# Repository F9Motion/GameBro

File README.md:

# GameBro
Custom portotive gaming console with Android OS, 5 buttons, joystick and display. I did this for playing minecraft Pocket edition and other games.

# Why I did this
I like minecraft and at school teachers before lesson take form students phones. This console is good for spent boring time (I don't play in lesson time don't worry)
# Features
1. This is full station for Android.
2. You can just install all games which you want and download to this!
3. Very cool :D.
4. With joystick you can control the mouse like in windows.
5. Compack: Easy to take outside
# How it works
The **Rodxa CM5** is full android station so almost all works do this Rodxa. And this 5 buttons and joystick connected to **Raspberry pi pico** and pico controls only this. **I don't place Wifi and Bluetooth module** because I don't think it's very important and you can just econome in this.
# How to assemble
1. Order PCB form JLCPCB
2. Order all parts for this GameBro (You can find parts in BOM)
3. Solder parts to PCB
4. Print CAD
5. And just assemble all of this
# Bill of Materials (BOM)
|Name                          |Cost   |Link                     |
|------------------------------|-------|-------------------------|
|Radxa cm5                     |$182.16|https://ali.click/m5rxp1e|
|Raspberry pi pico             |$3.47  |https://ali.click/i4rxp1a|
|Joystick                      |$0.92  |https://ali.click/q3rxp14|
|Buttons                       |$0.5   |https://ali.click/q2rxp1s|
|HDMI socket                   |$0.71  |https://ali.click/bdrxp15|
|Type-C socket                 |$1.02  |https://ali.click/cfrxp1w|
|Printing PCB                  |$4.20  |order from JLCPCB        |
|Felament price for 3D printing|       |                         |
|buttons.step                  |$0.01  |Printing legion          |
|bottom.step                   |$0.97  |Printing legion          |
|top.step                      |$0.21  |Printing legion          |
|TOTAL                         |$194.17|                         |
# Credits
All of work done by Rasul
# Sponsors
Hack club forge (https://forge.hackclub.com/)

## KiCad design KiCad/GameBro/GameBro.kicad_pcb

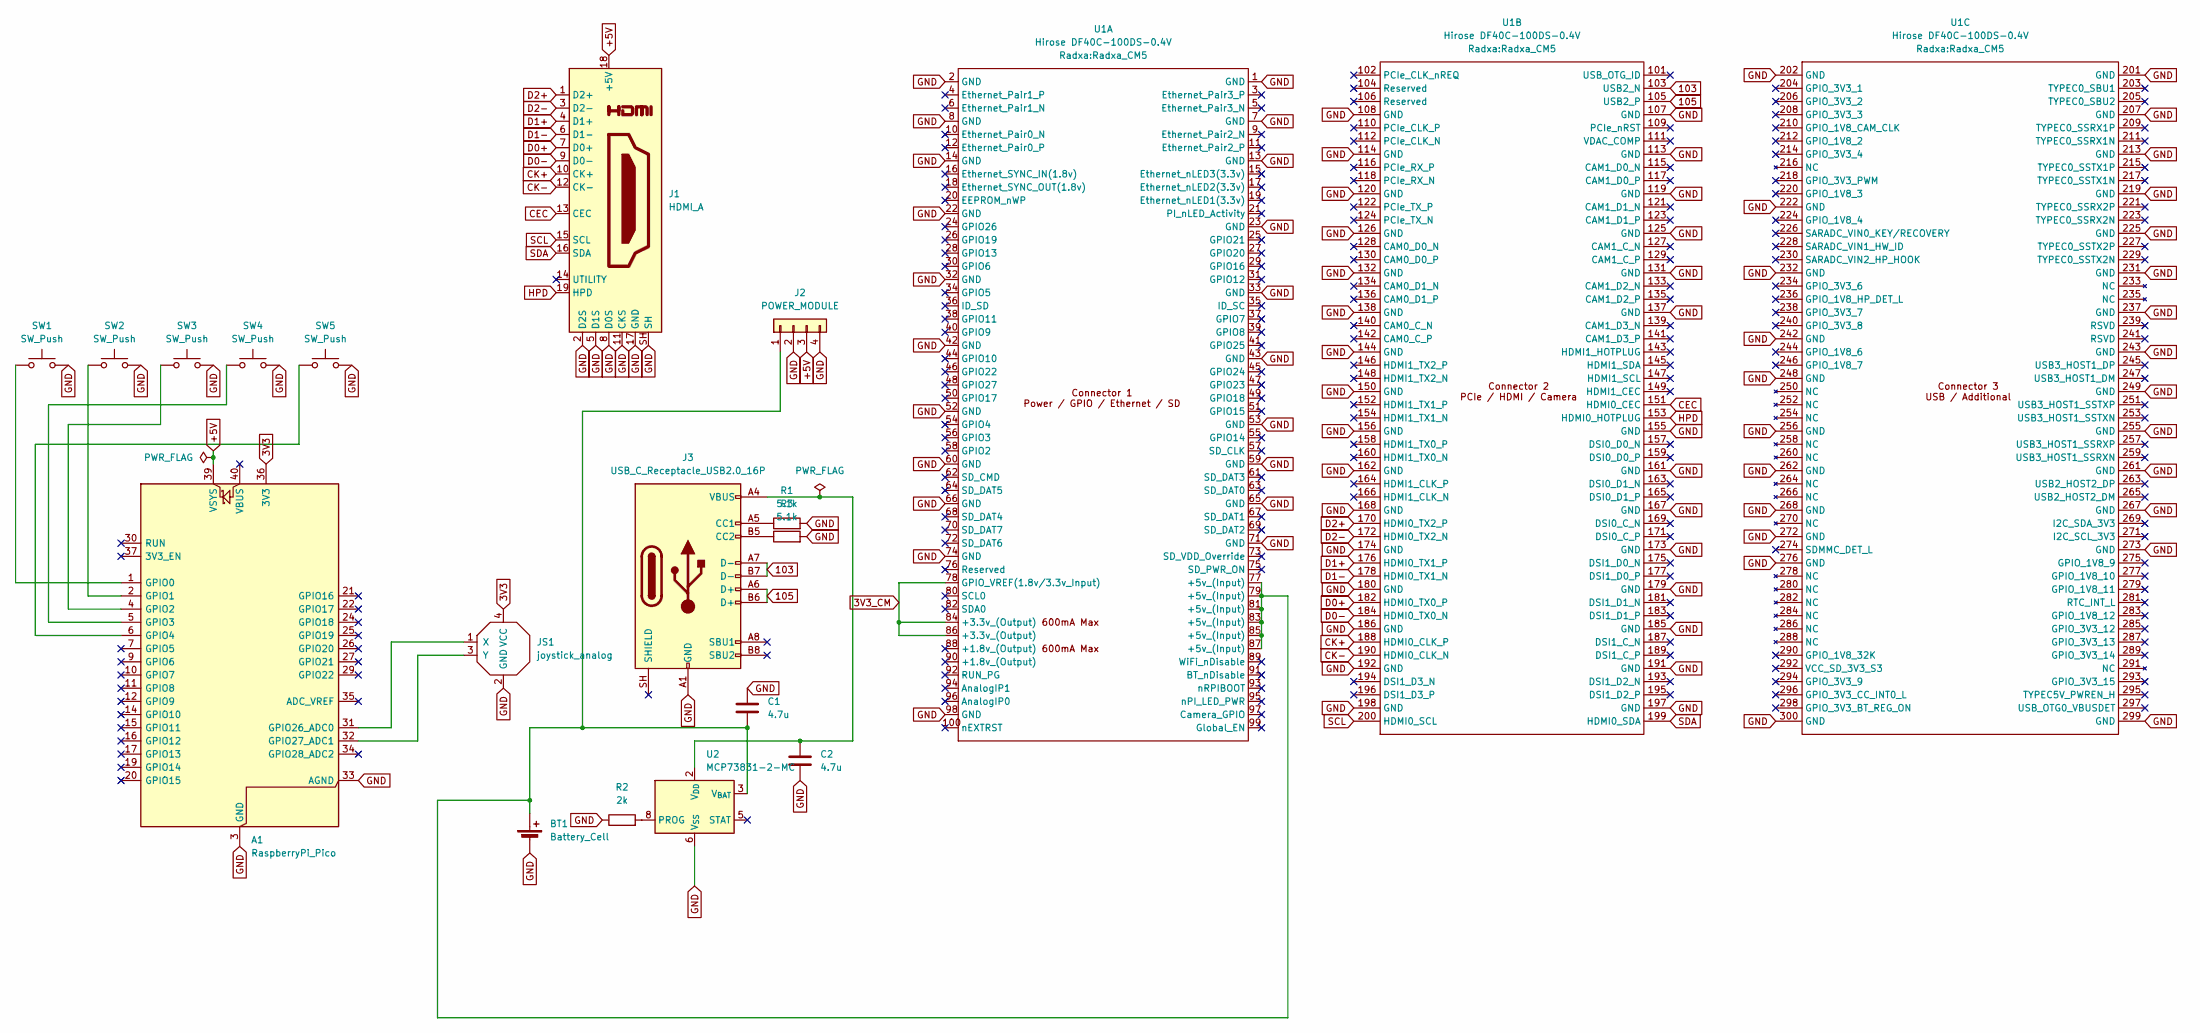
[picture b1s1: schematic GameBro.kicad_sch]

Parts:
A1: RaspberryPi_Pico; RaspberryPi_Pico_Common_Unspecified
BT1: Battery_Cell; JST_PH_B2B-PH-K_1x02_P2.00mm_Vertical
C1, C2: 4.7u; C_0805_2012Metric
J1: HDMI_A; HDMI_A_Molex_208658-1001_Horizontal
J2: POWER_MODULE; PinHeader_1x04_P2.54mm_Vertical
J3: USB_C_Receptacle_USB2.0_16P; USB_C_Receptacle_HRO_TYPE-C-31-M-12
JS1: joystick_analog; JOYSTICK-PSP1000
R1, R3: 5.1k; R_0603_1608Metric
R2: 2k; R_0603_1608Metric
SW1, SW2, SW3, SW4, SW5: SW_Push; SW_SPST_PTS810
U1: Hirose DF40C-100DS-0.4V; Radxa_CM5
U2: MCP73831-2-MC; Radxa_CM5

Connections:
3V3: A1.36 (3V3), JS1.4 (VCC)
3V3_CM: U1.78 (GPIO_VREF(1.8v/3.3v_Input)), U1.84 (+3.3v_(Output)), U1.86 (+3.3v_(Output))
103: J3.A7 (D-), J3.B7 (D-), U1.103 (USB2_N)
105: J3.A6 (D+), J3.B6 (D+), U1.105 (USB2_P)
+5V: A1.39 (VSYS), J1.18 (+5V), J2.3
CEC: J1.13 (CEC), U1.151 (HDMI0_CEC)
CK+: J1.10 (CK+), U1.188 (HDMI0_CLK_P)
CK-: J1.12 (CK-), U1.190 (HDMI0_CLK_N)
D0+: J1.7 (D0+), U1.182 (HDMI0_TX0_P)
D0-: J1.9 (D0-), U1.184 (HDMI0_TX0_N)
D1+: J1.4 (D1+), U1.176 (HDMI0_TX1_P)
D1-: J1.6 (D1-), U1.178 (HDMI0_TX1_N)
D2+: J1.1 (D2+), U1.170 (HDMI0_TX2_P)
D2-: J1.3 (D2-), U1.172 (HDMI0_TX2_N)
GND: A1.3 (GND), A1.8 (GND), A1.13 (GND), A1.18 (GND), A1.23 (GND), A1.28 (GND), A1.33 (AGND), A1.38 (GND), BT1.2 (-), C1.1, C2.2, J1.2 (D2S), J1.5 (D1S), J1.8 (D0S), J1.11 (CKS), J1.17 (GND), J1.SH, J2.2, J2.4, J3.A1 (GND), J3.A12 (GND), J3.B1 (GND), J3.B12 (GND), JS1.2 (GND), R1.2, R2.1, R3.2, SW1.2, SW2.2, SW3.2, SW4.2, SW5.2, U1.1 (GND), U1.2 (GND), U1.7 (GND), U1.8 (GND), U1.13 (GND), U1.14 (GND), U1.22 (GND), U1.23 (GND), U1.32 (GND), U1.33 (GND), U1.42 (GND), U1.43 (GND), U1.52 (GND), U1.53 (GND), U1.59 (GND), U1.60 (GND), U1.65 (GND), U1.66 (GND), U1.71 (GND), U1.74 (GND), U1.98 (GND), U1.107 (GND), U1.108 (GND), U1.113 (GND), U1.114 (GND), U1.119 (GND), U1.120 (GND), U1.125 (GND), U1.126 (GND), U1.131 (GND), U1.132 (GND), U1.137 (GND), U1.138 (GND), U1.144 (GND), U1.150 (GND), U1.155 (GND), U1.156 (GND), U1.161 (GND), U1.162 (GND), U1.167 (GND), U1.168 (GND), U1.173 (GND), U1.174 (GND), U1.179 (GND), U1.180 (GND), U1.185 (GND), U1.186 (GND), U1.191 (GND), U1.192 (GND), U1.197 (GND), U1.198 (GND), U1.201 (GND), U1.202 (GND), U1.207 (GND), U1.213 (GND), U1.219 (GND), U1.222 (GND), U1.225 (GND), U1.231 (GND), U1.232 (GND), U1.237 (GND), U1.242 (GND), U1.243 (GND), U1.248 (GND), U1.249 (GND), U1.255 (GND), U1.256 (GND), U1.261 (GND), U1.262 (GND), U1.267 (GND), U1.268 (GND), U1.272 (GND), U1.273 (GND), U1.276 (GND), U1.299 (GND), U1.300 (GND), U2.6 (V_{SS})
HPD: J1.19 (HPD), U1.153 (HDMI0_HOTPLUG)
unnamed: A1.1 (GPIO0), SW1.1
unnamed: A1.2 (GPIO1), SW2.1
unnamed: A1.4 (GPIO2), SW3.1
unnamed: A1.5 (GPIO3), SW4.1
unnamed: A1.6 (GPIO4), SW5.1
unnamed: A1.31 (GPIO26_ADC0), JS1.1 (X)
unnamed: A1.32 (GPIO27_ADC1), JS1.3 (Y)
unnamed: BT1.1 (+), C1.2, J2.1, U1.77 (+5v_(Input)), U1.79 (+5v_(Input)), U1.81 (+5v_(Input)), U1.83 (+5v_(Input)), U1.85 (+5v_(Input)), U1.87 (+5v_(Input)), U2.3 (V_{BAT}), U2.4 (V_{BAT})
unnamed: C2.1, J3.A4 (VBUS), J3.A9 (VBUS), J3.B4 (VBUS), J3.B9 (VBUS), U2.1 (V_{DD}), U2.2 (V_{DD})
unnamed: J3.A5 (CC1), R1.1
unnamed: J3.B5 (CC2), R3.1
unnamed: R2.2, U2.8 (PROG)
SCL: J1.15 (SCL), U1.200 (HDMI0_SCL)
SDA: J1.16 (SDA), U1.199 (HDMI0_SDA)

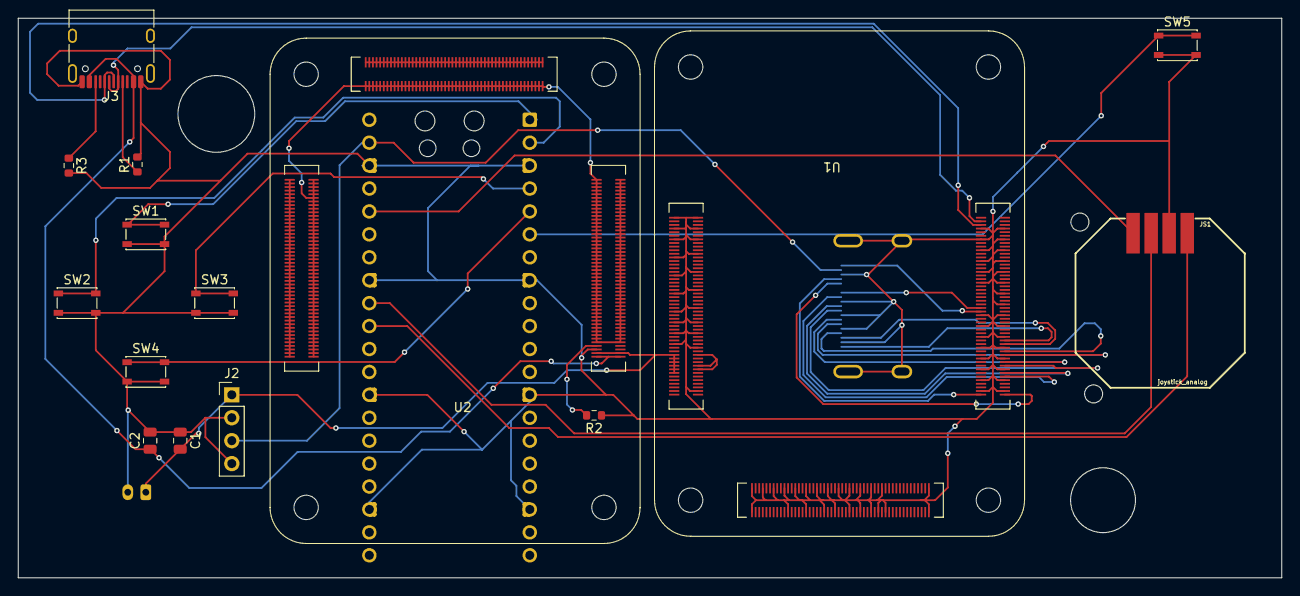
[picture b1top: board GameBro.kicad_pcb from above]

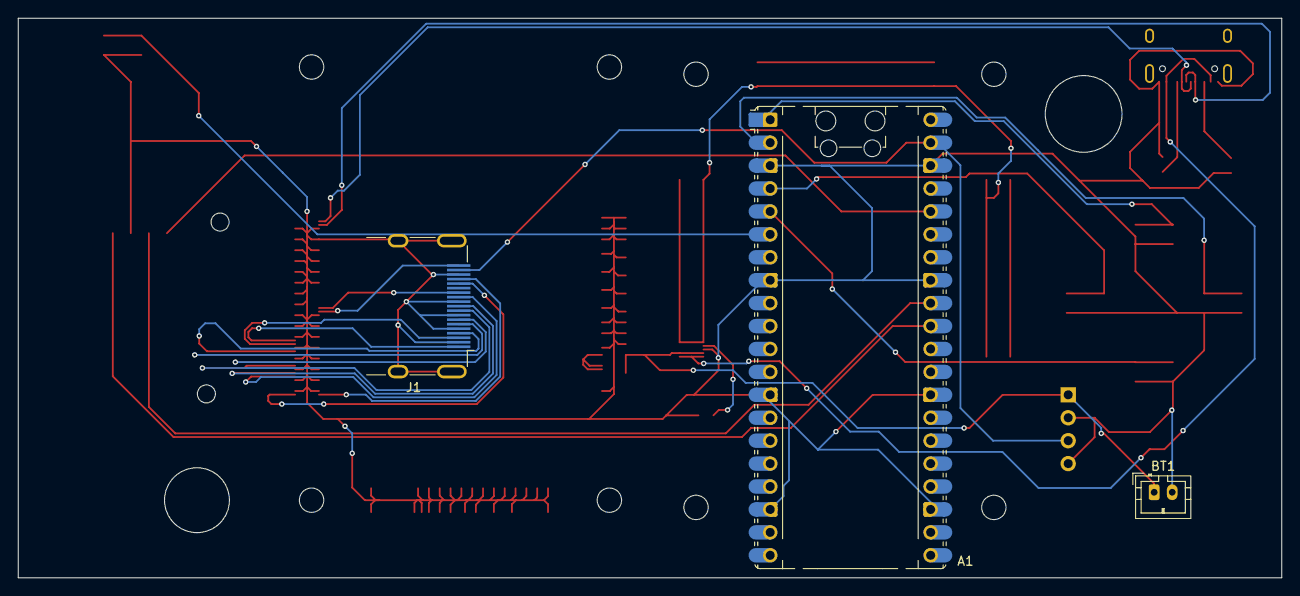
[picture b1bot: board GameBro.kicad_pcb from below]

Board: 2 copper layers, 140.0 x 62.0 mm, 18 parts (3 on the bottom side), 30 nets.
